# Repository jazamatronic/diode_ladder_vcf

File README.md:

# diode_ladder_vcf

A Diode Ladder VCF

Å voltage controlled lowpass diode ladder filter.
Cutoff and Res master knobs. Control voltage inputs for both Cutoff and Res, with attenuators.
Selectable resonance gain compensation mode so the volume stays relatively flat as resonance increases.
Selectable keyboard tracking mode and it self oscillates, so the filter can be played.
Has a soft-clipping overdrive circuit on the front-end, plus adjustable input attenuation.
Has a HP-like mode that works by subtracting the LP signal from the input - there's a front-panel pot to help tune this.

Tiny demo and snapshots here:

https://imgur.com/a/kTCuVp1

Inspiration taken from:
http://www.timstinchcombe.co.uk/index.php?pge=diode

https://www.instructables.com/Diode-Ladder-VCF-With-NO-PCB/

https://www.haraldswerk.de/Filter/NGF_Ladder/NGF_Ladder.html

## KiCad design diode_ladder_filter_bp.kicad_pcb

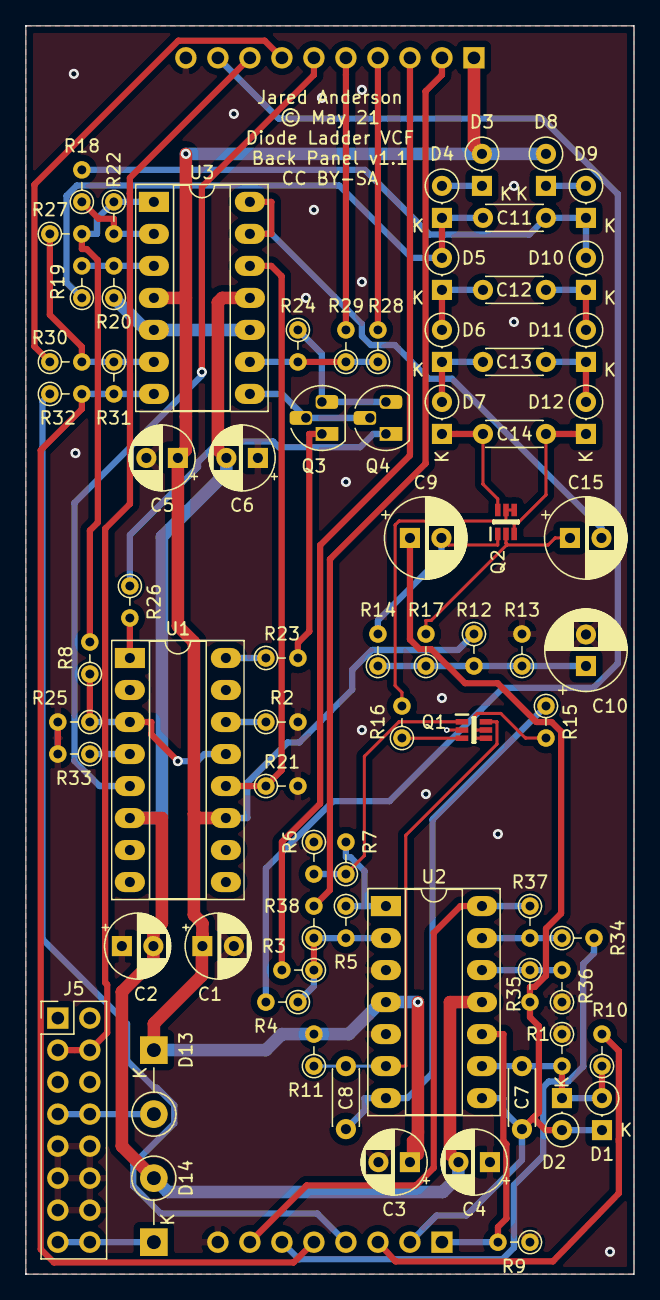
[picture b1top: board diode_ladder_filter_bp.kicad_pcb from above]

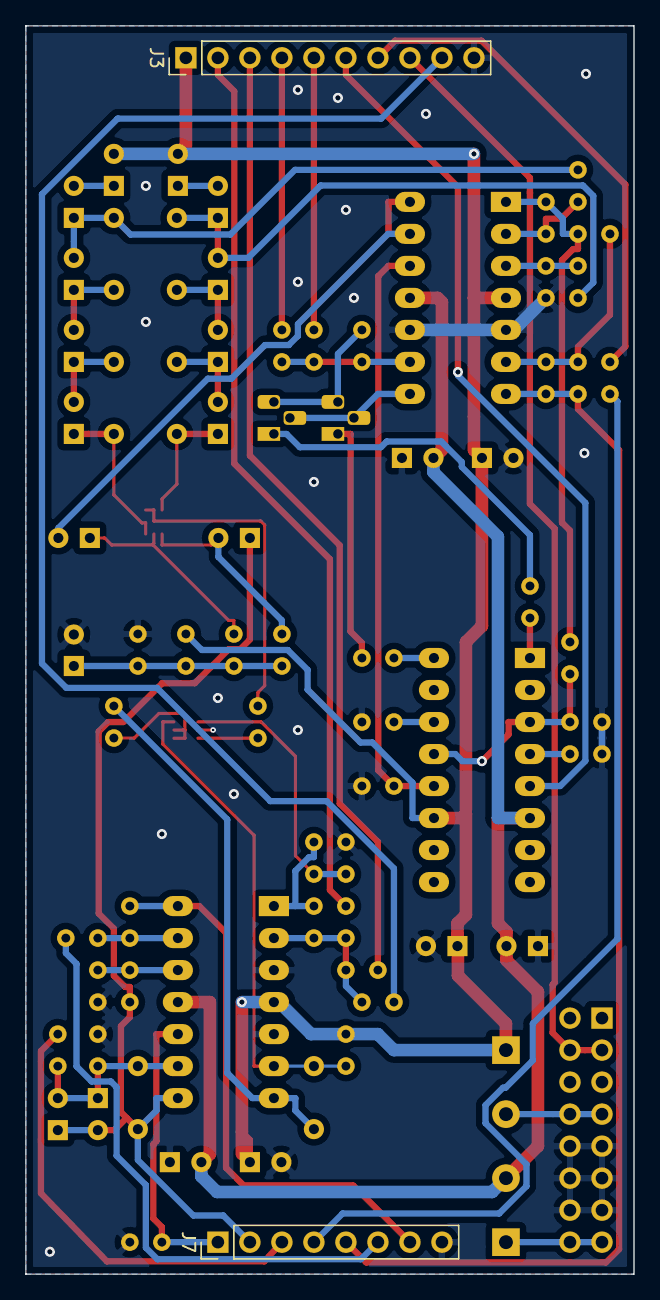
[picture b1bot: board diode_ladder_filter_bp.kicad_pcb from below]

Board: 2 copper layers, 48.3 x 99.1 mm, 77 parts (2 on the bottom side), 60 nets.

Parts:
C1, C2, C3, C4, C5, C6: 0.1u; CP_Radial_D5.0mm_P2.50mm
C7, C8: 22p; C_Disc_D4.3mm_W1.9mm_P5.00mm
C9, C15: 10u; CP_Radial_D6.3mm_P2.50mm
C10: 220u; CP_Radial_D6.3mm_P2.50mm
C11, C12, C13, C14: 100n; C_Disc_D4.3mm_W1.9mm_P5.00mm
D1, D2, D3, D4, D5, D6, D7, D8, D9, D10, D11, D12: 1N4148; D_DO-35_SOD27_P2.54mm_Vertical_KathodeUp
D13, D14: 1N5817; D_DO-41_SOD81_P5.08mm_Vertical_KathodeUp
J3: CON_TOP; PinHeader_1x10_P2.54mm_Vertical
J5: PWR_HDR; PinHeader_2x08_P2.54mm_Vertical
J7: CON_BTM; PinHeader_1x08_P2.54mm_Vertical
Q1, Q2: PMP4201Y,135; SOT65P210X110-6N
Q3, Q4: BC557; TO-92_HandSolder
R1, R2, R25, R33: 2k2; R_Axial_DIN0204_L3.6mm_D1.6mm_P2.54mm_Vertical
R3, R4, R38: 100k; R_Axial_DIN0204_L3.6mm_D1.6mm_P2.54mm_Vertical
R5: 2k; R_Axial_DIN0204_L3.6mm_D1.6mm_P2.54mm_Vertical
R6: 900; R_Axial_DIN0204_L3.6mm_D1.6mm_P2.54mm_Vertical
R7: 100; R_Axial_DIN0204_L3.6mm_D1.6mm_P2.54mm_Vertical
R8, R12, R18, R19, R20, R22, R28, R29, R34, R35: 10k; R_Axial_DIN0204_L3.6mm_D1.6mm_P2.54mm_Vertical
R9, R16, R23, R26: 470; R_Axial_DIN0204_L3.6mm_D1.6mm_P2.54mm_Vertical
R10: 4k7; R_Axial_DIN0204_L3.6mm_D1.6mm_P2.54mm_Vertical
R11: 1M2; R_Axial_DIN0204_L3.6mm_D1.6mm_P2.54mm_Vertical
R13, R14, R17, R32: 1k; R_Axial_DIN0204_L3.6mm_D1.6mm_P2.54mm_Vertical
R15: 7k5; R_Axial_DIN0204_L3.6mm_D1.6mm_P2.54mm_Vertical
R21: 75k; R_Axial_DIN0204_L3.6mm_D1.6mm_P2.54mm_Vertical
R24: 47k; R_Axial_DIN0204_L3.6mm_D1.6mm_P2.54mm_Vertical
R27, R30: 22k; R_Axial_DIN0204_L3.6mm_D1.6mm_P2.54mm_Vertical
R31: 470k; R_Axial_DIN0204_L3.6mm_D1.6mm_P2.54mm_Vertical
R36, R37: 220k; R_Axial_DIN0204_L3.6mm_D1.6mm_P2.54mm_Vertical
U1: LM13700; DIP-16_W7.62mm_Socket_LongPads
U2, U3: TL074; DIP-14_W7.62mm_Socket_LongPads

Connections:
+12V: C1.1, C3.1, C5.1, D3.2, D8.2, D13.1, J3.1, R11.2, R12.1, U1.11, U2.4, U3.4
-12V: C2.2, C4.2, C6.2, D14.2, U1.6, U2.11, U3.11
GND: C1.2, C2.1, C3.2, C4.1, C5.2, C6.1, C10.2, J3.10, J5.9, J5.10, J5.11, J5.12, J5.13, J5.14, J7.8, Q1.2, R1.1, R2.2, R6.1, R9.1, R13.2, R20.1, R21.2, R25.2, R33.2, R36.1, U2.3, U2.5, U3.5, U3.10
I_RES_COMP: Q4.1, R26.1
unnamed: C7.1, D1.2, D2.1, R1.2, R10.1, U2.9
unnamed: C8.1, R15.1, U2.7
unnamed: C8.2, Q1.6, R11.1, U2.6
unnamed: C9.2, Q2.1, R14.2
unnamed: C10.1, R12.2, R13.1, R14.1, R17.1
unnamed: C12.1, D10.1, D11.2
unnamed: C12.2, D5.1, D6.2
unnamed: C13.1, D11.1, D12.2
unnamed: C13.2, D6.1, D7.2
unnamed: C14.1, D12.1, Q2.3
unnamed: C14.2, D7.1, Q2.6
unnamed: C15.1, Q2.2, R17.2
unnamed: C15.2, U3.13, U3.14
unnamed: D3.1, D4.2
unnamed: D8.1, D9.2
unnamed: D13.2, J5.7, J5.8
unnamed: D14.1, J5.15, J5.16
unnamed: Q1.1, R6.2, R7.1
unnamed: Q1.3, R16.1
unnamed: Q1.4, Q1.5, R15.2
unnamed: Q2.4, Q2.5, R16.2
unnamed: Q3.1, R23.2
unnamed: Q3.2, Q4.2, U3.8
unnamed: Q3.3, Q4.3, R24.1
unnamed: R2.1, U1.14
unnamed: R3.1, R4.1, R5.2, R38.1, U2.2
unnamed: R5.1, R7.2, U2.1
unnamed: R18.1, R22.2, U3.2
unnamed: R19.2, R20.2, U3.3
unnamed: R21.1, U1.12, U3.12
unnamed: R8.2, R22.1, R27.2, U3.1
unnamed: R23.1, U1.16
unnamed: R24.2, R28.1, R29.1, U3.9
unnamed: R8.1, R25.1, U1.3, U1.13
unnamed: R26.2, U1.1
unnamed: R27.1, R30.2, R31.1, U3.6
unnamed: R33.1, U1.4
unnamed: R34.1, R37.2, U2.13
unnamed: R35.1, R36.2, U2.12
VIN_ATTEN: J7.1, R9.2, U2.10
VOUT_HP: J7.7, R37.1, U2.14
VOUT_LP: J7.4, R32.1
VOUT_NEG: C11.2, D4.1, D5.2, R19.1
VOUT_POS: C11.1, D9.1, D10.2, R18.2
V_DRIVE: C7.2, C9.1, D1.1, D2.2, J7.2, R35.2, U2.8
V_DRIVE_FB_ATTEN: J7.3, R10.2
V_FC: J3.2, R38.2
V_FC_CV: J3.3, R3.2
V_FC_KB: J3.8, J5.3, J5.4
V_FC_KB_SW: J3.9, R4.2
V_OUT_LP_: J7.5, R31.2, R32.2, U3.7
V_RES: J3.4, R28.2
V_RES_CV: J3.5, R29.2
V_RES_FB: J3.6, U1.5
V_RES_FB_SW: J3.7, R30.1
V_TO_HP: J7.6, R34.2

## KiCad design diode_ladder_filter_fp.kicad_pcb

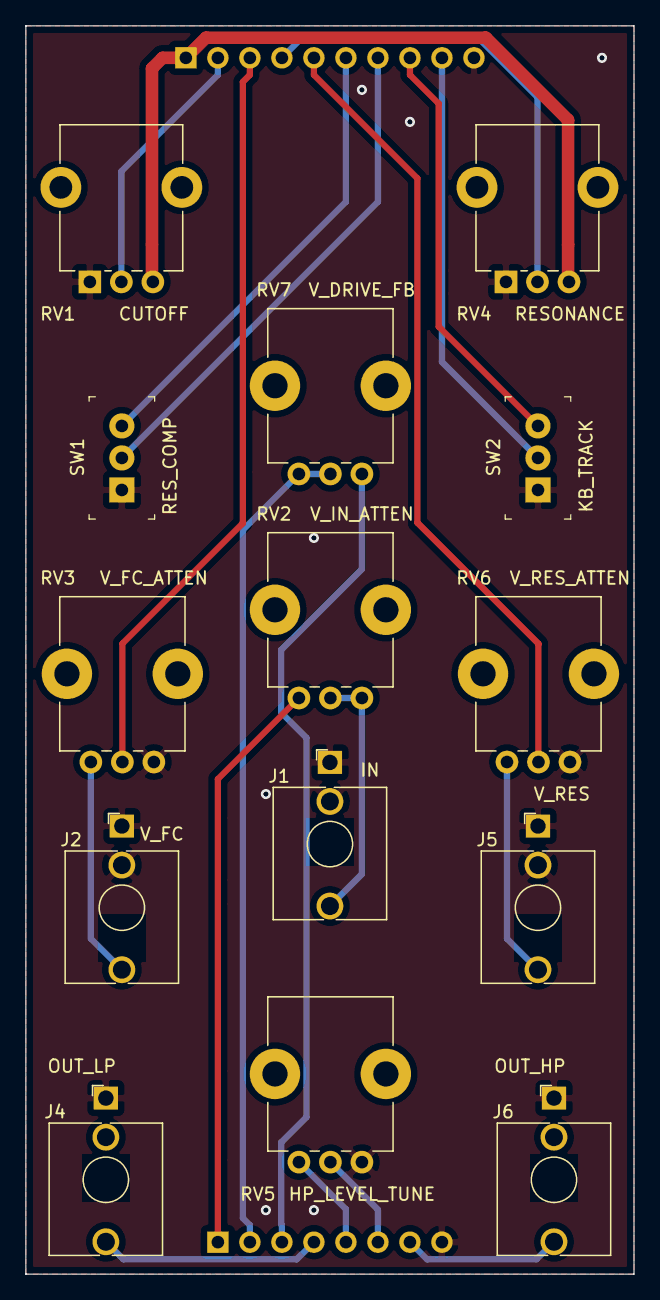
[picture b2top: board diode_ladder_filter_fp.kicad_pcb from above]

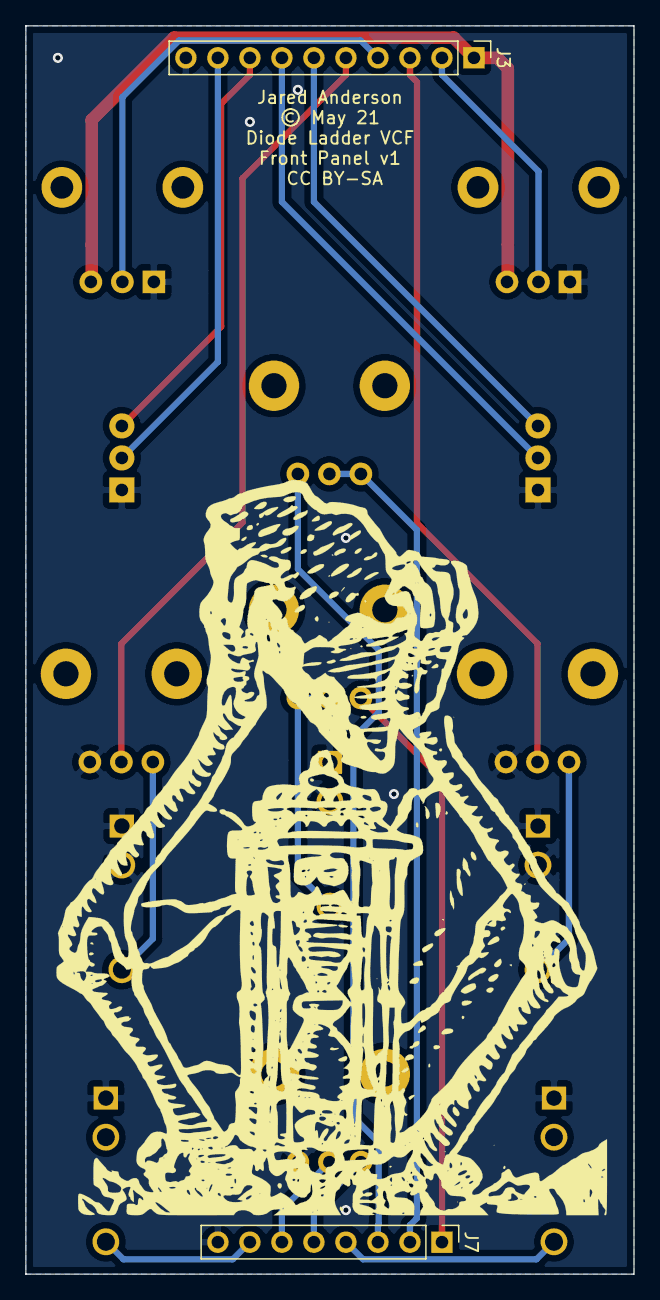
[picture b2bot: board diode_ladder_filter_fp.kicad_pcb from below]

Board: 2 copper layers, 48.3 x 99.1 mm, 16 parts (2 on the bottom side), 20 nets.

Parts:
J1: IN; Jack_3.5mm_QingPu_WQP-PJ398SM_Vertical_CircularHoles
J2: V_FC; Jack_3.5mm_QingPu_WQP-PJ398SM_Vertical_CircularHoles
J3: CON_TOP; PinHeader_1x10_P2.54mm_Vertical
J4: OUT_LP; Jack_3.5mm_QingPu_WQP-PJ398SM_Vertical_CircularHoles
J5: V_RES; Jack_3.5mm_QingPu_WQP-PJ398SM_Vertical_CircularHoles
J6: OUT_HP; Jack_3.5mm_QingPu_WQP-PJ398SM_Vertical_CircularHoles
J7: CON_BTM; PinHeader_1x08_P2.54mm_Vertical
RV1, RV4: 100k; Potentiometer_Alpha_RD901F-40-00D_Single_Vertical_CircularH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
RV2, RV3, RV5, RV6, RV7: 100k; Potentiometer_Bourns_PTV09A-1_Single_Vertical
SW1, SW2: SW_SPDT; Switch_Toggle_ATE1D-2M3-10-Z

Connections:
+12V: J3.1, RV1.3, RV4.3
GND: J1.S, J1.TN, J2.S, J2.TN, J3.10, J4.S, J5.S, J5.TN, J6.S, J7.8, RV1.1, RV3.1, RV4.1, RV5.1, RV6.1, SW1.1, SW2.1
unnamed: J1.T, RV2.1, RV2.2
unnamed: J2.T, RV3.3
unnamed: J5.T, RV6.3
VIN_ATTEN: J7.1, RV2.3
VOUT_HP: J6.T, J7.7
VOUT_LP: J4.T, J7.4
V_DRIVE_FB: J7.2, RV7.2, RV7.3
V_DRIVE_FB_ATTEN: J7.3, RV7.1
V_FC: J3.2, RV1.2
V_FC_CV: J3.3, RV3.2
V_FC_KB: J3.8, SW2.3
V_FC_KB_SW: J3.9, SW2.2
V_OUT_LP_: J7.5, RV5.3
V_RES: J3.4, RV4.2
V_RES_CV: J3.5, RV6.2
V_RES_FB: J3.6, SW1.3
V_RES_FB_SW: J3.7, SW1.2
V_TO_HP: J7.6, RV5.2

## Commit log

2021-05-30 Added details - schematics and PCBs

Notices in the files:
diode_ladder_filter_bp.kicad_pcb:
© May 21
CC BY-SA
